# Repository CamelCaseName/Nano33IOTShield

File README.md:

# Nano33IOTShield
A shield for the Arduino nano 33 IOT to shifts it's GPIO from 3.3v to 5v with an integrated HUB75 plug

See the [bill of materials](/BOM.txt) for what to get.

The [HUB75nano](https://github.com/CamelCaseName/HUB75nano) library will be updated to support this hat and arduino combination.

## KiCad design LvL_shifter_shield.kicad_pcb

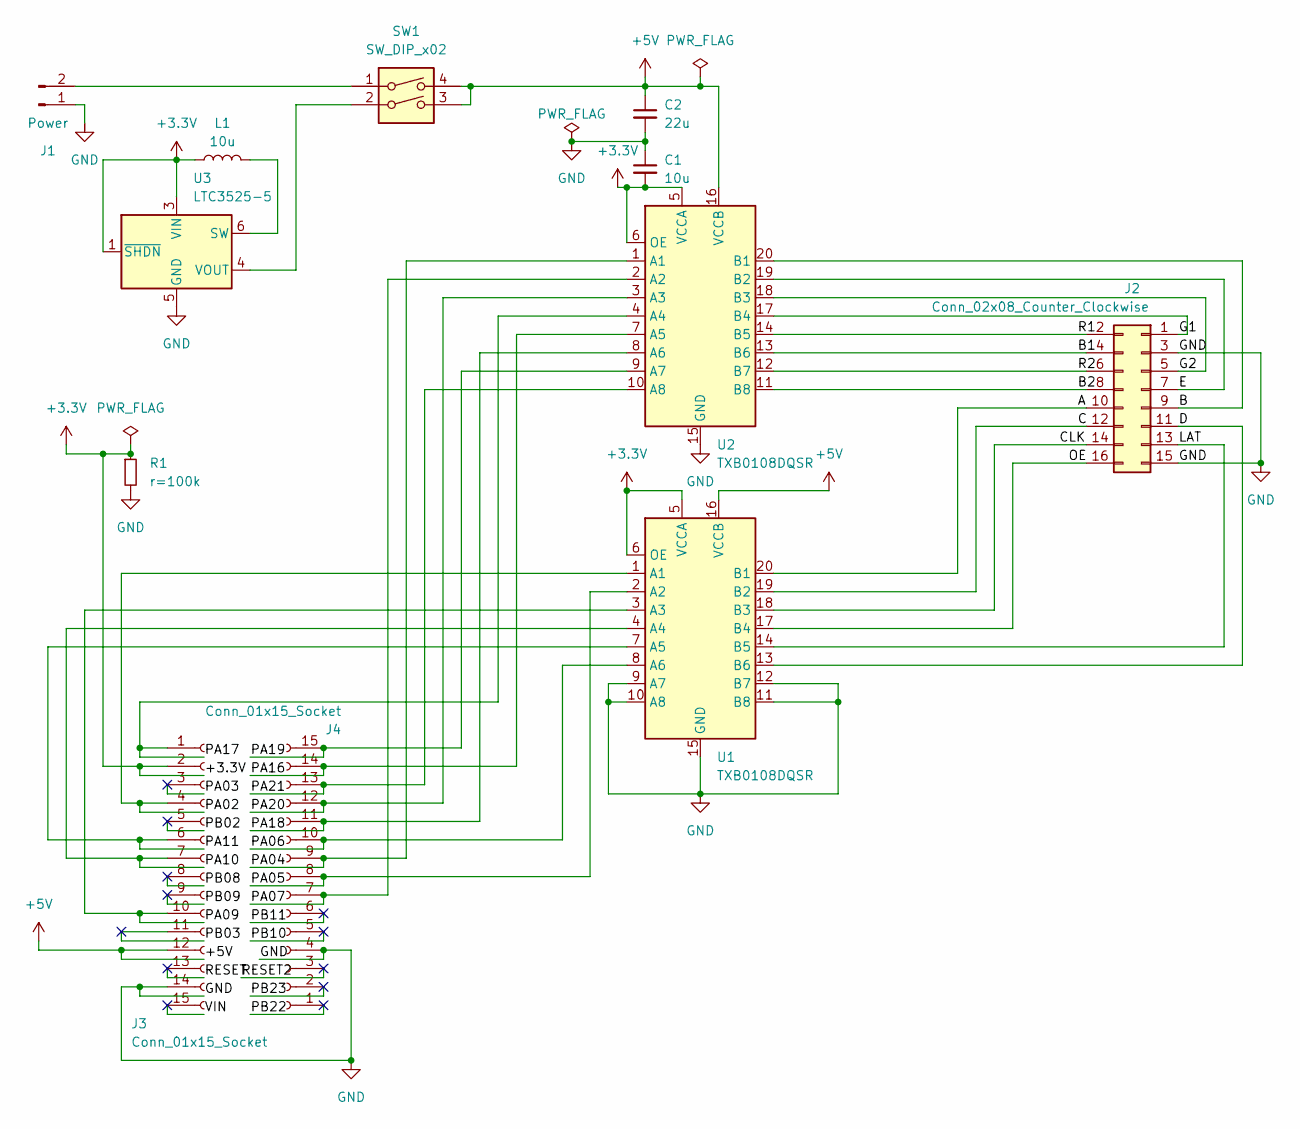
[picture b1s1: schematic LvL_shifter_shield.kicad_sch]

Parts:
C1: 10u; C_1206_3216Metric_Pad1.33x1.80mm_HandSolder
C2: 22u; C_1206_3216Metric_Pad1.33x1.80mm_HandSolder
J1: Power; JST_EH_S2B-EH_1x02_P2.50mm_Horizontal
J2: Conn_02x08_Counter_Clockwise; PinSocket_2x08_P2.54mm_Vertical
J3, J4: Conn_01x15_Socket; PinSocket_1x15_P2.54mm_Vertical
L1: 10u; L_1008_2520Metric_Pad1.43x2.20mm_HandSolder
R1: r=100k; R_1206_3216Metric_Pad1.30x1.75mm_HandSolder
SW1: SW_DIP_x02; SW_DIP_SPSTx02_Slide_Copal_CHS-02A_W5.08mm_P1.27mm_JPin
U1, U2: TXB0108DQSR; USON-20_2x4mm_P0.4mm
U3: LTC3525-5; SOT-363_SC-70-6

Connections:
+3.3V: C1.2, J3.2, L1.1, R1.1, U1.5 (VCCA), U1.6 (OE), U2.5 (VCCA), U2.6 (OE), U3.1 (~SHDN), U3.3 (VIN)
+5V: C2.1, J3.12, SW1.3, SW1.4, U1.16 (VCCB), U2.16 (VCCB)
/A: J2.10, U1.20 (B1)
/B: J2.9, U2.20 (B1)
/B1: J2.4, U2.13 (B6)
/B2: J2.8, U2.11 (B8)
/C: J2.12, U1.19 (B2)
/CLK: J2.14, U1.18 (B3)
/D: J2.11, U1.13 (B6)
/E: J2.7, U2.19 (B2)
/G1: J2.1, U2.17 (B4)
/G2: J2.5, U2.18 (B3)
/LAT: J2.13, U1.14 (B5)
/OE: J2.16, U1.17 (B4)
/PA02: J3.4, U1.1 (A1)
/PA03: J3.3
/PA04: J4.9, U2.1 (A1)
/PA05: J4.8, U1.2 (A2)
/PA06: J4.10, U1.8 (A6)
/PA07: J4.7, U2.2 (A2)
/PA09: J3.10, U1.3 (A3)
/PA10: J3.7, U1.4 (A4)
/PA11: J3.6, U1.7 (A5)
/PA16: J4.14, U2.7 (A5)
/PA17: J3.1, U2.4 (A4)
/PA18: J4.11, U2.8 (A6)
/PA19: J4.15, U2.9 (A7)
/PA20: J4.12, U2.3 (A3)
/PA21: J4.13, U2.10 (A8)
/PB02: J3.5
/PB03: J3.11
/PB08: J3.8
/PB09: J3.9
/PB10: J4.5
/PB11: J4.6
/PB22: J4.1
/PB23: J4.2
/R1: J2.2, U2.14 (B5)
/R2: J2.6, U2.12 (B7)
/RESET: J3.13
/RESET2: J4.3
/VIN: J3.15
GND: C1.1, C2.2, J1.1, J2.3, J2.15, J3.14, J4.4, R1.2, U1.9 (A7), U1.10 (A8), U1.11 (B8), U1.12 (B7), U1.15 (GND), U2.15 (GND), U3.2 (GND), U3.5 (GND)
unnamed: J1.2, SW1.1
unnamed: L1.2, U3.6 (SW)
unnamed: SW1.2, U3.4 (VOUT)

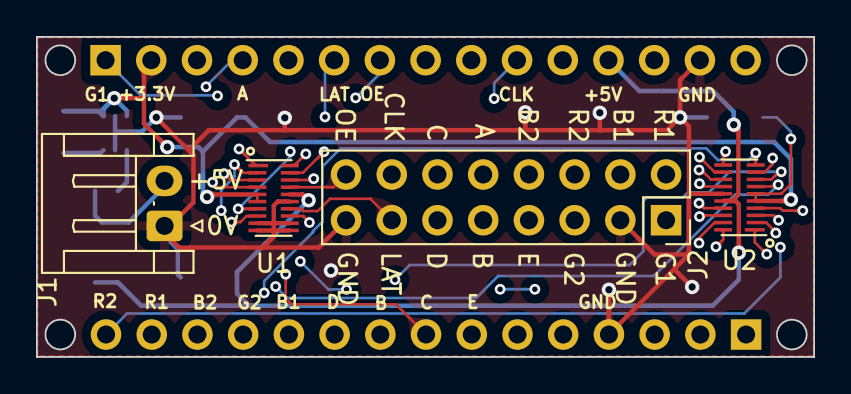
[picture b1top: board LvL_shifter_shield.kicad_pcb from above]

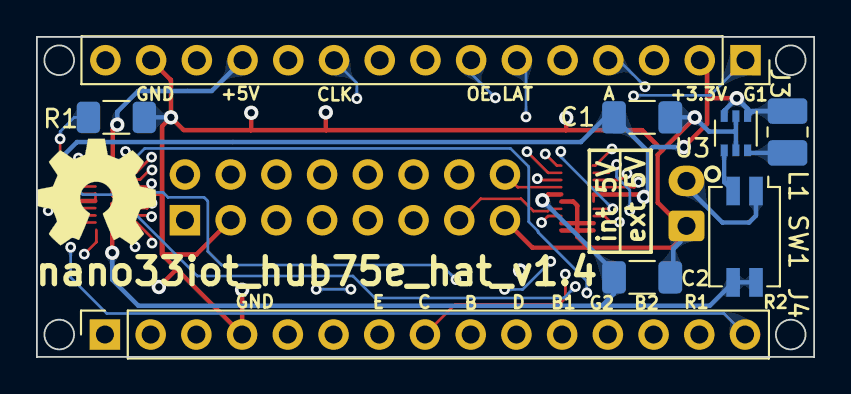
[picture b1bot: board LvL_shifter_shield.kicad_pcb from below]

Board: 4 copper layers, 43.2 x 17.8 mm, 12 parts (8 on the bottom side), 34 nets.

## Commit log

2023-11-15 Added files
2023-11-16 Updated silkscreen and added a +5 link to the nano
2023-11-16 Forgot to set OE high when power is connected
    You can work around this with a jumper wire from 3.3v to the OE side of the R1 and R2
2023-11-17 Updated version number, added open hardware logo
2023-11-26 switched pin PA03 and PA02, added internal 5V
    the dip switch can be used to get external 5v, internal or when none is selected the usb 5v from the arduino
2023-12-01 fixed drill files
